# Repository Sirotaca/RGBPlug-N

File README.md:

# RGBPlug Type N
Compact DE-15 ("VGA") adapter for the SNES/SFC-style AV multi-out. Video timing is unchanged, so a monitor or video processor compatible with 15 kHz RGB is required. The switch toggles between separate H/V sync or composite sync output.

For the NTSC SNES/SFC or PAL GameCube, populate C6-C11 but do not populate R6-R8. For the PAL SNES, populate R6-R8 and bridge the pads of C6-C11.

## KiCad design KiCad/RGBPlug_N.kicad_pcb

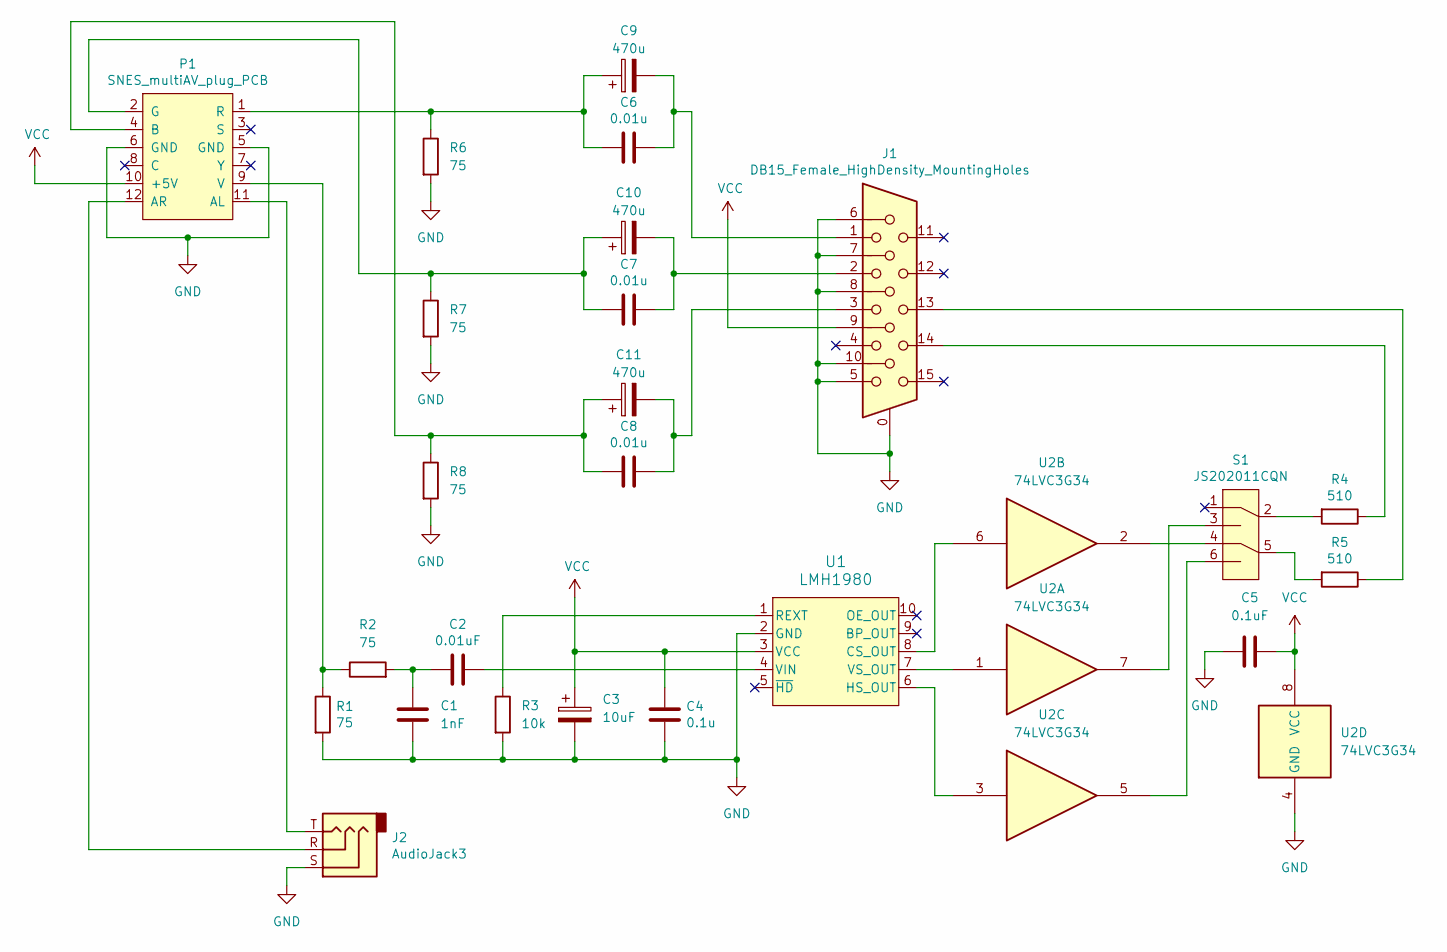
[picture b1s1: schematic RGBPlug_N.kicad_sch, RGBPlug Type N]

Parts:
C1: 1nF; C_0805_2012Metric_Pad1.18x1.45mm_HandSolder
C2: 0.01uF; C_0805_2012Metric_Pad1.18x1.45mm_HandSolder
C3: 10uF; C_1206_3216Metric_Pad1.33x1.80mm_HandSolder
C4: 0.1u; C_0805_2012Metric_Pad1.18x1.45mm_HandSolder
C5: 0.1uF; C_0805_2012Metric_Pad1.18x1.45mm_HandSolder
C6, C7, C8: 0.01u; C_0805_2012Metric_Pad1.18x1.45mm_HandSolder
C9, C10, C11: 470u; CP_Radial_D6.3mm_P2.50mm
J1: DB15_Female_HighDensity_MountingHoles; L17HTHES4F1C
J2: AudioJack3; Jack_3.5mm_CUI_SJ1-3533NG_Horizontal
P1: SNES_multiAV_plug_PCB
R1, R2, R6, R7, R8: 75; R_0805_2012Metric_Pad1.20x1.40mm_HandSolder
R3: 10k; R_0805_2012Metric_Pad1.20x1.40mm_HandSolder
R4, R5: 510; R_0805_2012Metric_Pad1.20x1.40mm_HandSolder
S1: JS202011CQN; SW_CuK_JS202011CQN_DPDT_Straight
U1: LMH1980; VSSOP-10_3x3mm_P0.5mm
U2: 74LVC3G34; TSSOP-8_3x3mm_P0.65mm

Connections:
GND: C1.2, C3.2, C4.1, C5.1, J1.0, J1.5, J1.6, J1.7, J1.8, J1.10, J2.S, P1.5 (GND), P1.6 (GND), R1.2, R3.2, R6.2, R7.2, R8.2, U1.2 (GND), U2.4 (GND)
unnamed: C1.1, C2.2, R2.2
unnamed: C6.1, C9.2, J1.1
unnamed: C7.1, C10.2, J1.2
unnamed: C8.2, C11.2, J1.3
unnamed: J1.13, R5.1
unnamed: J1.14, R4.1
unnamed: J2.T, P1.11 (AL)
unnamed: J2.R, P1.12 (AR)
unnamed: C8.1, C11.1, P1.4 (B), R8.1
unnamed: C7.2, C10.1, P1.2 (G), R7.1
unnamed: C6.2, C9.1, P1.1 (R), R6.1
unnamed: P1.9 (V), R1.1, R2.1
unnamed: R4.2, S1.2
unnamed: R5.2, S1.5
unnamed: S1.3, U2.7
unnamed: S1.4, U2.2
unnamed: S1.6, U2.5
unnamed: U1.8 (CS_OUT), U2.6
unnamed: U1.6 (HS_OUT), U2.3
unnamed: R3.1, U1.1 (REXT)
unnamed: C2.1, U1.4 (VIN)
unnamed: U1.7 (VS_OUT), U2.1
VCC: C3.1, C4.2, C5.2, J1.9, P1.10 (+5V), U1.3 (VCC), U2.8 (VCC)

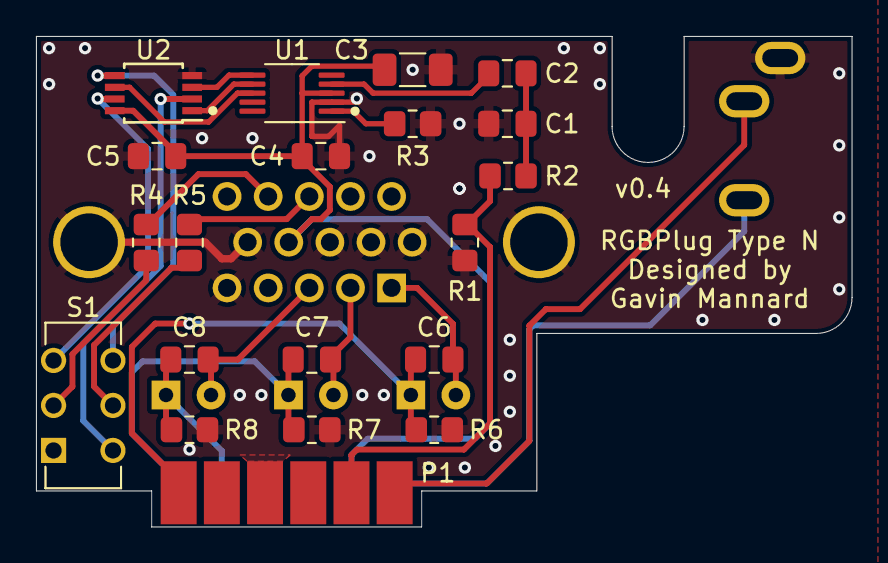
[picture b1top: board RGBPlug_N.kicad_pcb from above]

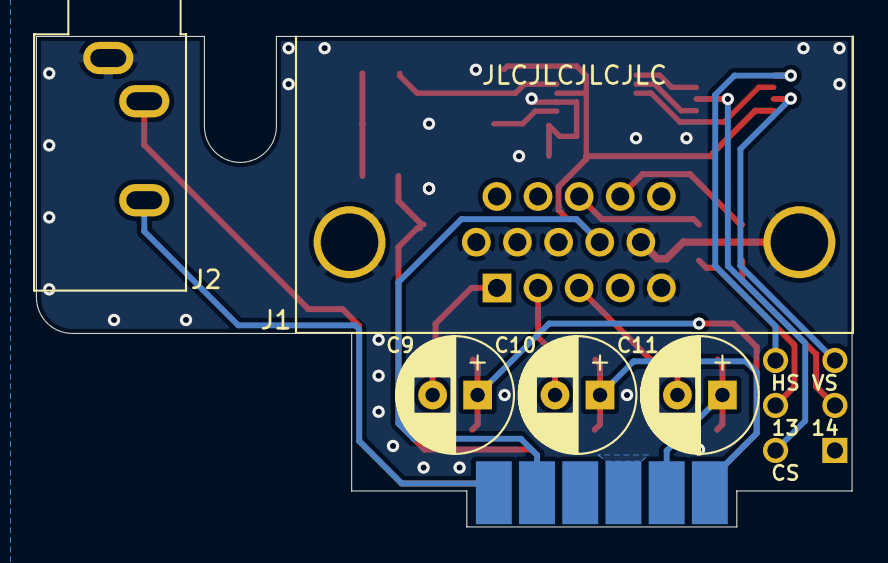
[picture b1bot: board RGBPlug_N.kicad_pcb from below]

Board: 2 copper layers, 45.3 x 27.2 mm, 25 parts (5 on the bottom side), 24 nets.

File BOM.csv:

"Reference","Value","Datasheet","Footprint","Qty","DNP"
"C1","1nF","~","Capacitor_SMD:C_0805_2012Metric_Pad1.18x1.45mm_HandSolder","1",""
"C2","0.01uF","~","Capacitor_SMD:C_0805_2012Metric_Pad1.18x1.45mm_HandSolder","1",""
"C3","10uF","~","Capacitor_SMD:C_1206_3216Metric_Pad1.33x1.80mm_HandSolder","1",""
"C4","0.1u","~","Capacitor_SMD:C_0805_2012Metric_Pad1.18x1.45mm_HandSolder","1",""
"C5","0.1uF","~","Capacitor_SMD:C_0805_2012Metric_Pad1.18x1.45mm_HandSolder","1",""
"C6,C7,C8","0.01u","~","Capacitor_SMD:C_0805_2012Metric_Pad1.18x1.45mm_HandSolder","3",""
"C9,C10,C11","470u","~","Capacitor_THT:CP_Radial_D6.3mm_P2.50mm","3",""
"J1","DB15_Female_HighDensity_MountingHoles"," ~","retro_gaming:L17HTHES4F1C","1",""
"J2","AudioJack3","~","Connector_Audio:Jack_3.5mm_CUI_SJ1-3533NG_Horizontal","1",""
"P1","SNES_multiAV_plug_PCB","","retro_gaming:SNES_multiAV_plug_PCB","1",""
"R1,R2,R6,R7,R8","75","~","Resistor_SMD:R_0805_2012Metric_Pad1.20x1.40mm_HandSolder","5",""
"R3","10k","~","Resistor_SMD:R_0805_2012Metric_Pad1.20x1.40mm_HandSolder","1",""
"R4,R5","510","~","Resistor_SMD:R_0805_2012Metric_Pad1.20x1.40mm_HandSolder","2",""
"S1","JS202011CQN","https://www.ckswitches.com/media/1422/js.pdf","Button_Switch_THT:SW_CuK_JS202011CQN_DPDT_Straight","1",""
"U1","LMH1980","LMH1980","Package_SO:VSSOP-10_3x3mm_P0.5mm","1",""
"U2","74LVC3G34","http://www.ti.com/lit/sg/scyt129e/scyt129e.pdf","Package_SO:TSSOP-8_3x3mm_P0.65mm","1",""
